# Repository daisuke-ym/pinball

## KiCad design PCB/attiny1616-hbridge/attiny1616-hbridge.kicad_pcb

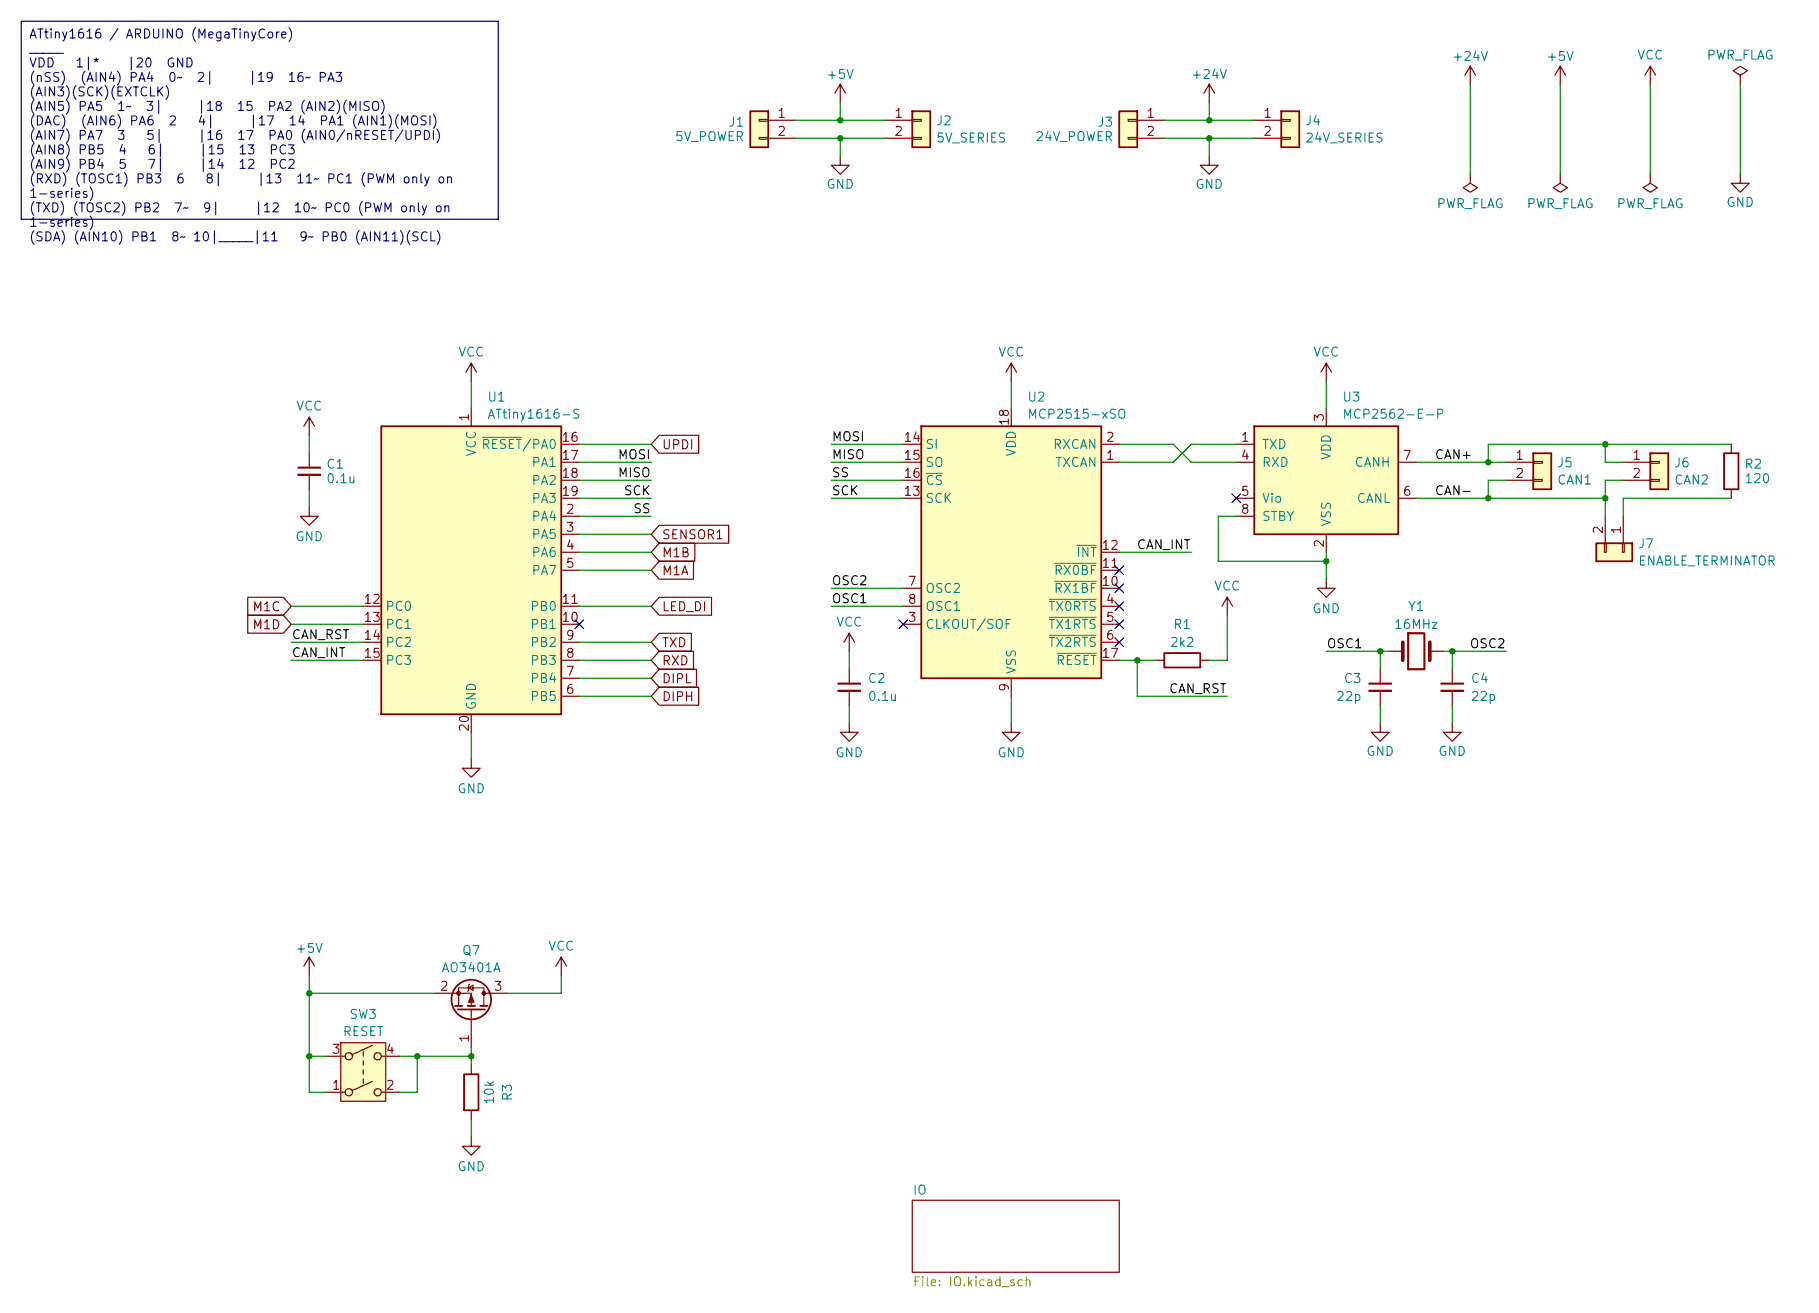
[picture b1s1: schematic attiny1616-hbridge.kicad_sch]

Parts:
C1, C2: 0.1u; C_0402_1005Metric; LCSC C307331
C3, C4: 22p; C_0402_1005Metric; LCSC C1555
J1: 5V_POWER; JST_XH_B2B-XH-A_1x02_P2.50mm_Vertical
J2: 5V_SERIES; JST_XH_B2B-XH-A_1x02_P2.50mm_Vertical
J3: 24V_POWER; JST_XH_B2B-XH-A_1x02_P2.50mm_Vertical
J4: 24V_SERIES; JST_XH_B2B-XH-A_1x02_P2.50mm_Vertical
J5: CAN1; JST_XH_B2B-XH-A_1x02_P2.50mm_Vertical
J6: CAN2; JST_XH_B2B-XH-A_1x02_P2.50mm_Vertical
J7: ENABLE_TERMINATOR; PinHeader_1x02_P2.54mm_Vertical
Q7: AO3401A; SOT-23; LCSC C15127
R1: 2k2; R_0402_1005Metric; LCSC C25879
R2: 120; R_0402_1005Metric; LCSC C25079
R3: 10k; R_0402_1005Metric; LCSC C25744
SW3: RESET; DTS-6-V-2
U1: ATtiny1616-S; SOIC-20W_7.5x12.8mm_P1.27mm
U2: MCP2515-xSO; DIP-18_W7.62mm_Socket
U3: MCP2562-E-P; DIP-8_W7.62mm
Y1: 16MHz; Crystal_SMD_3225-4Pin_3.2x2.5mm; LCSC C13738

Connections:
+5V: J1.1, J2.1, Q7.2 (S), SW3.1, SW3.3; also elsewhere on the board
+24V: J3.1, J4.1; also elsewhere on the board
/CAN+: J5.1, J6.1, R2.2, U3.7 (CANH)
/CAN-: J5.2, J6.2, J7.2, U3.6 (CANL)
/CAN_INT: U1.15 (PC3), U2.12 (~INT)
/CAN_RST: R1.1, U1.14 (PC2), U2.17 (~RESET)
/MISO: U1.18 (PA2), U2.15 (SO)
/MOSI: U1.17 (PA1), U2.14 (SI)
/OSC1: C3.1, U2.8 (OSC1), Y1.1
/OSC2: C4.1, U2.7 (OSC2), Y1.2
/SCK: U1.19 (PA3), U2.13 (SCK)
/SS: U1.2 (PA4), U2.16 (~CS)
DIPH: U1.6 (PB5); also elsewhere on the board
DIPL: U1.7 (PB4); also elsewhere on the board
GND: C1.2, C2.2, C3.2, C4.2, J1.2, J2.2, J3.2, J4.2, R3.2, U1.20 (GND), U2.9 (VSS), U3.2 (VSS), U3.8 (STBY); also elsewhere on the board
LED_DI: U1.11 (PB0); also elsewhere on the board
M1A: U1.5 (PA7); also elsewhere on the board
M1B: U1.4 (PA6); also elsewhere on the board
M1C: U1.12 (PC0); also elsewhere on the board
M1D: U1.13 (PC1); also elsewhere on the board
unnamed: J7.1, R2.1
unnamed: Q7.1 (G), R3.1, SW3.2, SW3.4
unnamed: U2.2 (RXCAN), U3.4 (RXD)
unnamed: U2.1 (TXCAN), U3.1 (TXD)
RXD: U1.8 (PB3); also elsewhere on the board
SENSOR1: U1.3 (PA5); also elsewhere on the board
TXD: U1.9 (PB2); also elsewhere on the board
UPDI: U1.16 (~RESET/PA0); also elsewhere on the board
VCC: C1.1, C2.1, Q7.3 (D), R1.2, U1.1 (VCC), U2.18 (VDD), U3.3 (VDD)

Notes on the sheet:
ATtiny1616 / ARDUINO (MegaTinyCore) _____ VDD 1|* |20 GND (nSS) (AIN4) PA4 0~ 2| |19 16~ PA3 (AIN3)(SCK)(EXTCLK) (AIN5) PA5 1~ 3| |18 15 PA2 (AIN2)(MISO) (DAC) (AIN6) PA6 2 4| |17 14 PA1 (AIN1)(MOSI) (AIN7) PA7 3 5| |16 17 PA0 (AIN0/nRESET/UPDI) (AIN8) PB5 4 6| |15 13 PC3 (AIN9) PB4 5 7| |14 12 PC2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

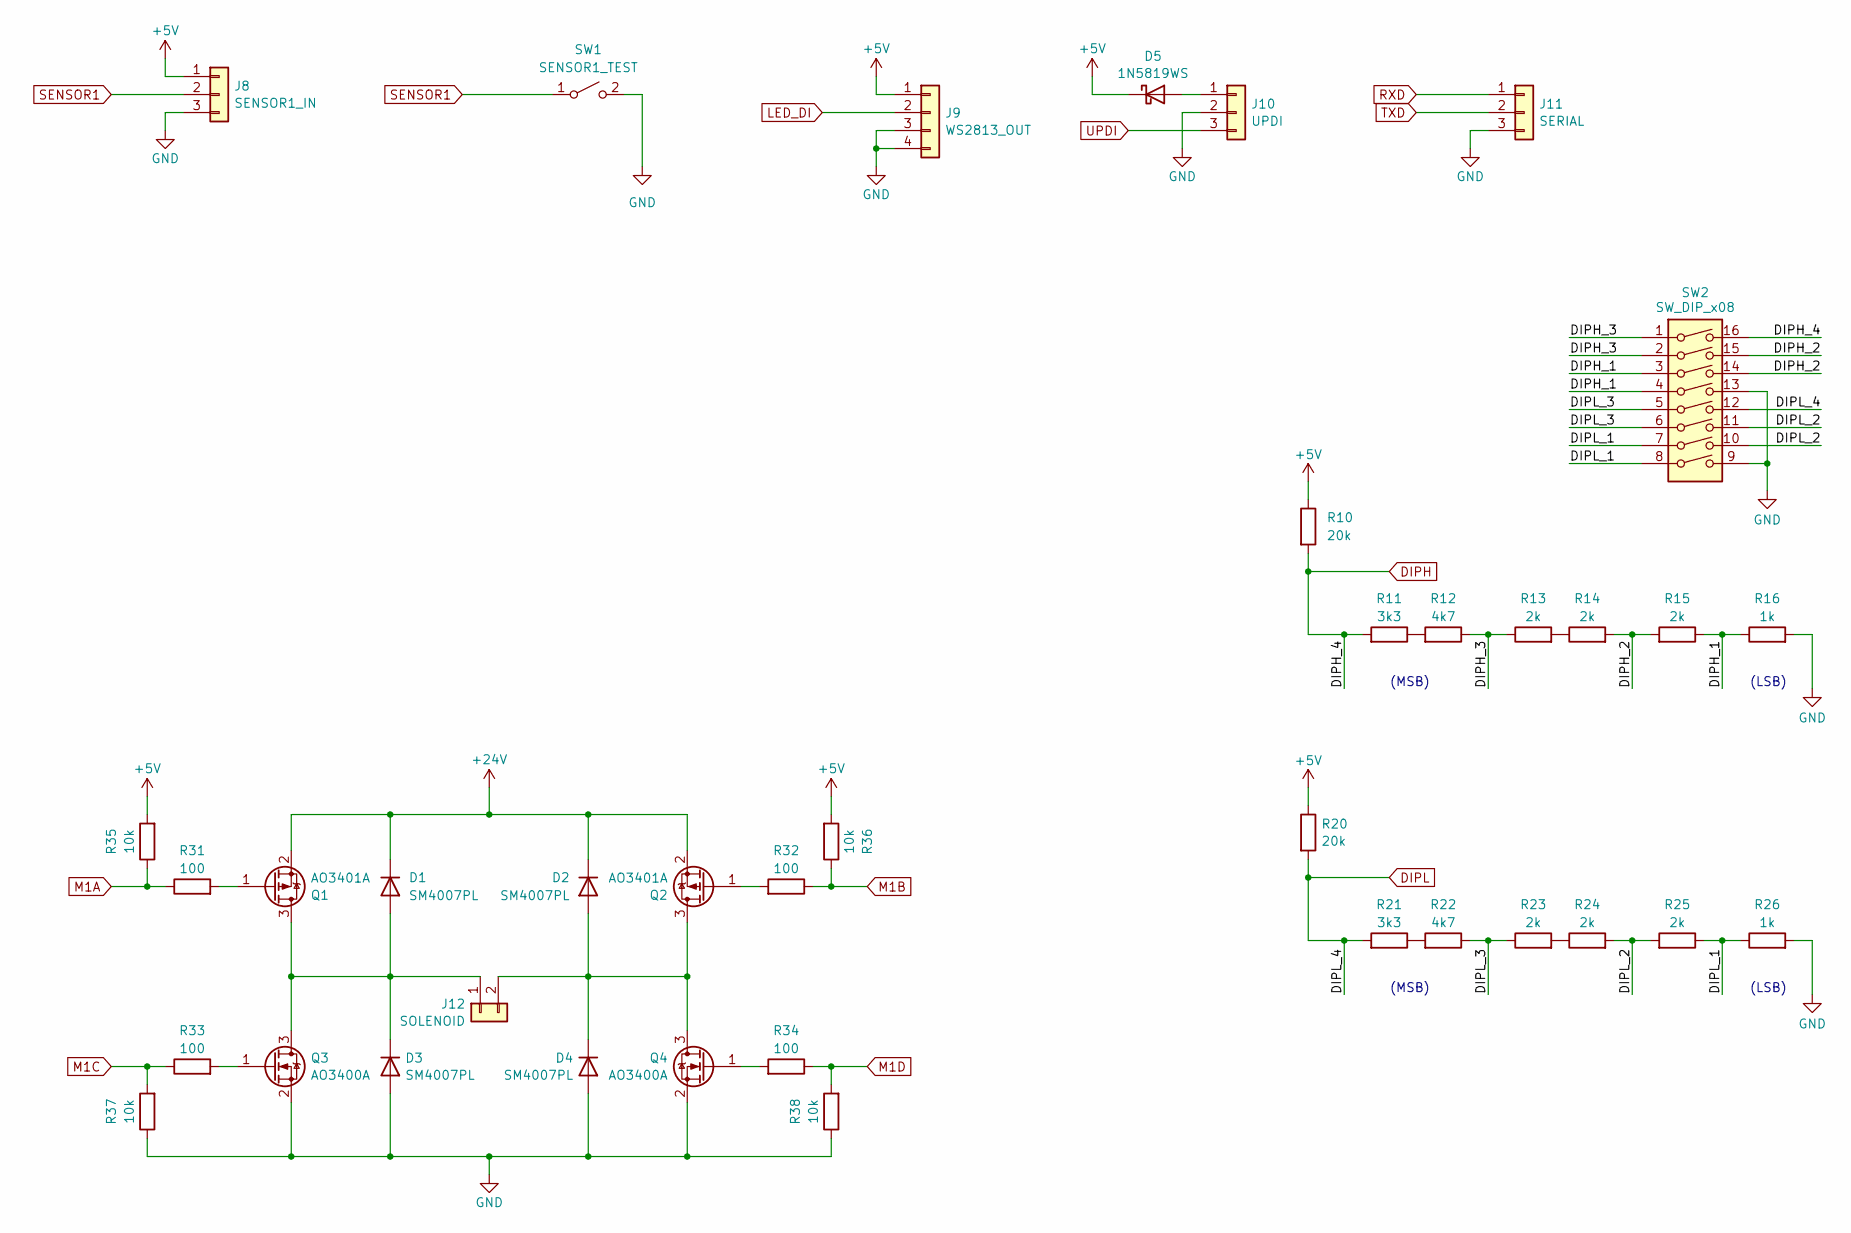
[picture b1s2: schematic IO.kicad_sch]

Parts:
D1, D2, D3, D4: SM4007PL; D_SOD-123F; LCSC C64898
D5: 1N5819WS; D_SOD-323; LCSC C191023
J8: SENSOR1_IN; JST_XH_B3B-XH-A_1x03_P2.50mm_Vertical
J9: WS2813_OUT; JST_XH_B4B-XH-A_1x04_P2.50mm_Vertical
J10: UPDI; PinHeader_1x03_P2.54mm_Vertical
J11: SERIAL; PinHeader_1x03_P2.54mm_Vertical
J12: SOLENOID; TB111-2-2
Q1, Q2: AO3401A; SOT-23; LCSC C15127
Q3, Q4: AO3400A; SOT-23; LCSC C20917
R10, R20: 20k; R_0402_1005Metric; LCSC C25765
R11, R21: 3k3; R_0402_1005Metric; LCSC C25890
R12, R22: 4k7; R_0402_1005Metric; LCSC C25900
R13, R14, R15, R23, R24, R25: 2k; R_0402_1005Metric; LCSC C4109
R16, R26: 1k; R_0402_1005Metric; LCSC C11702
R31, R32, R33, R34: 100; R_0402_1005Metric; LCSC C25077
R35, R36, R37, R38: 10k; R_0402_1005Metric; LCSC C25744
SW1: SENSOR1_TEST; TS-1088-AR02016; LCSC C720477
SW2: SW_DIP_x08; SW_DIP_SPSTx08_Slide_9.78x22.5mm_W7.62mm_P2.54mm

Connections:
+5V: D5.1 (K), J8.1, J9.1, R10.1, R20.1, R35.2, R36.2; also elsewhere on the board
+24V: D1.1 (K), D2.1 (K), Q1.2 (S), Q2.2 (S); also elsewhere on the board
/IO/DIPH_1: R15.1, R16.1, SW2.3, SW2.4
/IO/DIPH_2: R14.2, R15.2, SW2.14, SW2.15
/IO/DIPH_3: R12.1, R13.1, SW2.1, SW2.2
/IO/DIPL_1: R25.1, R26.1, SW2.7, SW2.8
/IO/DIPL_2: R24.2, R25.2, SW2.10, SW2.11
/IO/DIPL_3: R22.1, R23.1, SW2.5, SW2.6
DIPH: R10.2, R11.2, SW2.16; also elsewhere on the board
DIPL: R20.2, R21.2, SW2.12; also elsewhere on the board
GND: D3.2 (A), D4.2 (A), J8.3, J9.3, J9.4, J10.2, J11.3, Q3.2 (S), Q4.2 (S), R16.2, R26.2, R37.1, R38.1, SW1.2 (B), SW2.9, SW2.13; also elsewhere on the board
LED_DI: J9.2; also elsewhere on the board
M1A: R31.1, R35.1; also elsewhere on the board
M1B: R32.1, R36.1; also elsewhere on the board
M1C: R33.1, R37.2; also elsewhere on the board
M1D: R34.1, R38.2; also elsewhere on the board
unnamed: D1.2 (A), D3.1 (K), J12.1, Q1.3 (D), Q3.3 (D)
unnamed: D2.2 (A), D4.1 (K), J12.2, Q2.3 (D), Q4.3 (D)
unnamed: D5.2 (A), J10.1
unnamed: Q1.1 (G), R31.2
unnamed: Q2.1 (G), R32.2
unnamed: Q3.1 (G), R33.2
unnamed: Q4.1 (G), R34.2
unnamed: R11.1, R12.2
unnamed: R13.2, R14.1
unnamed: R21.1, R22.2
unnamed: R23.2, R24.1
RXD: J11.1; also elsewhere on the board
SENSOR1: J8.2, SW1.1 (A); also elsewhere on the board
TXD: J11.2; also elsewhere on the board
UPDI: J10.3; also elsewhere on the board

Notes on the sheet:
(LSB)
(MSB)

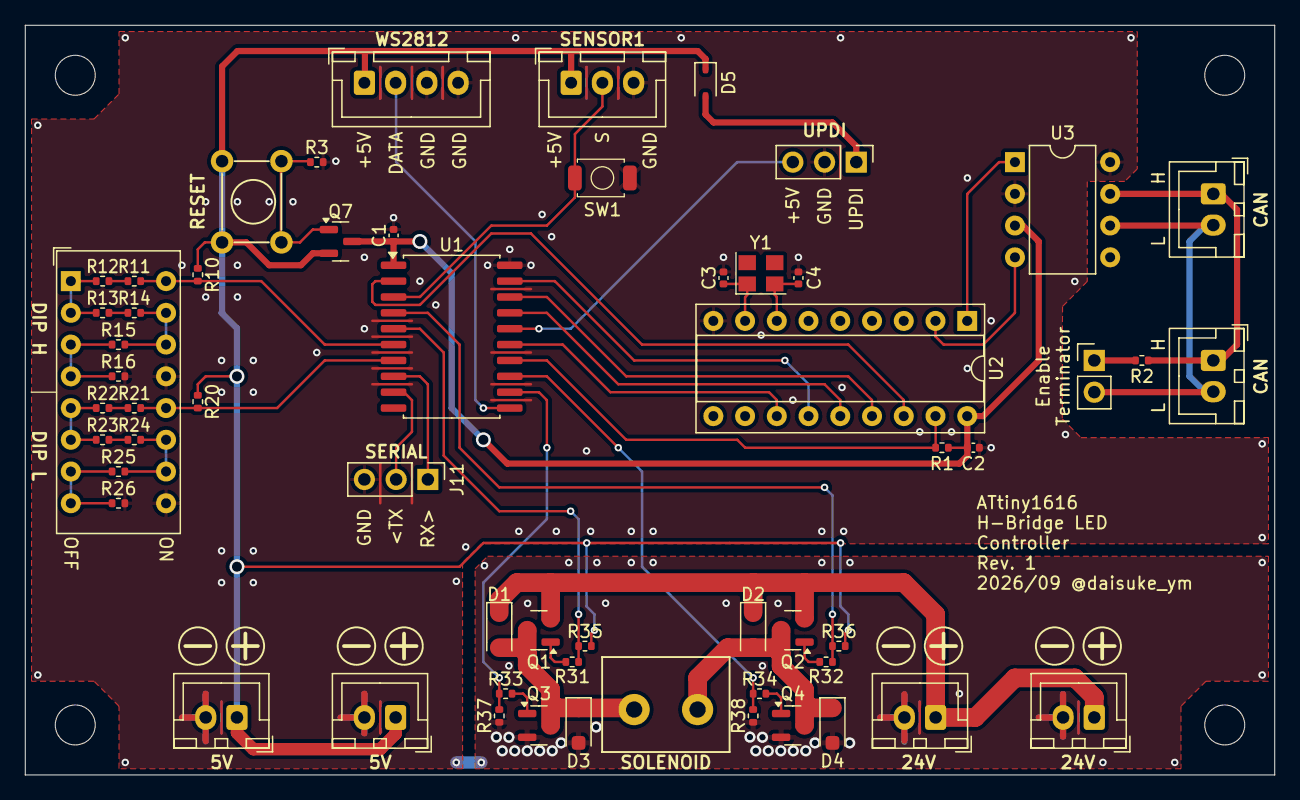
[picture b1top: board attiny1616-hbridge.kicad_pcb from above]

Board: 2 copper layers, 100.0 x 60.0 mm, 58 parts (0 on the bottom side), 46 nets.

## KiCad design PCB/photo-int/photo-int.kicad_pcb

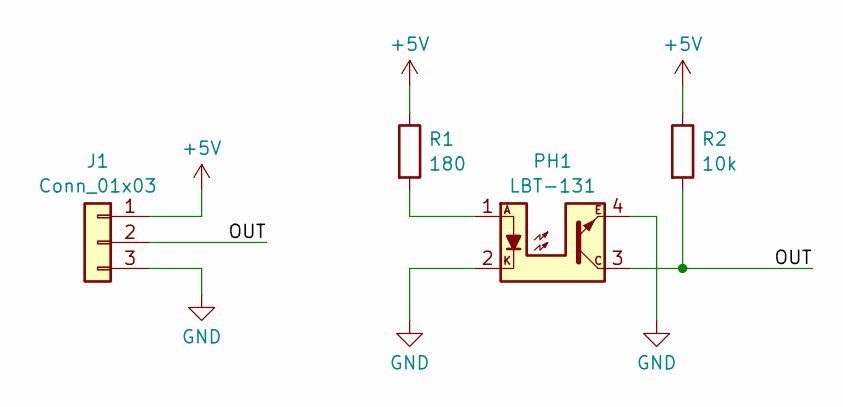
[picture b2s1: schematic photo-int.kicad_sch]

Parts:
J1: Conn_01x03; PinHeader_1x03_P2.54mm_Vertical
PH1: LBT-131
R1: 180; R_0603_1608Metric_Pad0.98x0.95mm_HandSolder
R2: 10k; R_0603_1608Metric_Pad0.98x0.95mm_HandSolder

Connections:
+5V: J1.1, R1.1, R2.1
/OUT: J1.2, PH1.3, R2.2
GND: J1.3, PH1.2, PH1.4
unnamed: PH1.1, R1.2

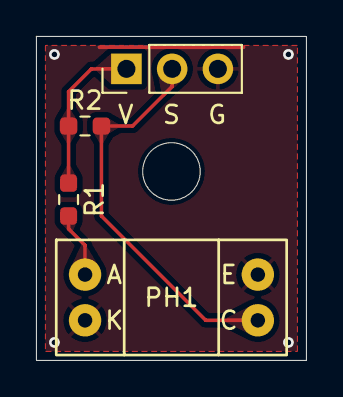
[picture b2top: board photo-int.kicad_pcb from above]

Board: 2 copper layers, 15.0 x 18.0 mm, 4 parts (0 on the bottom side), 4 nets.

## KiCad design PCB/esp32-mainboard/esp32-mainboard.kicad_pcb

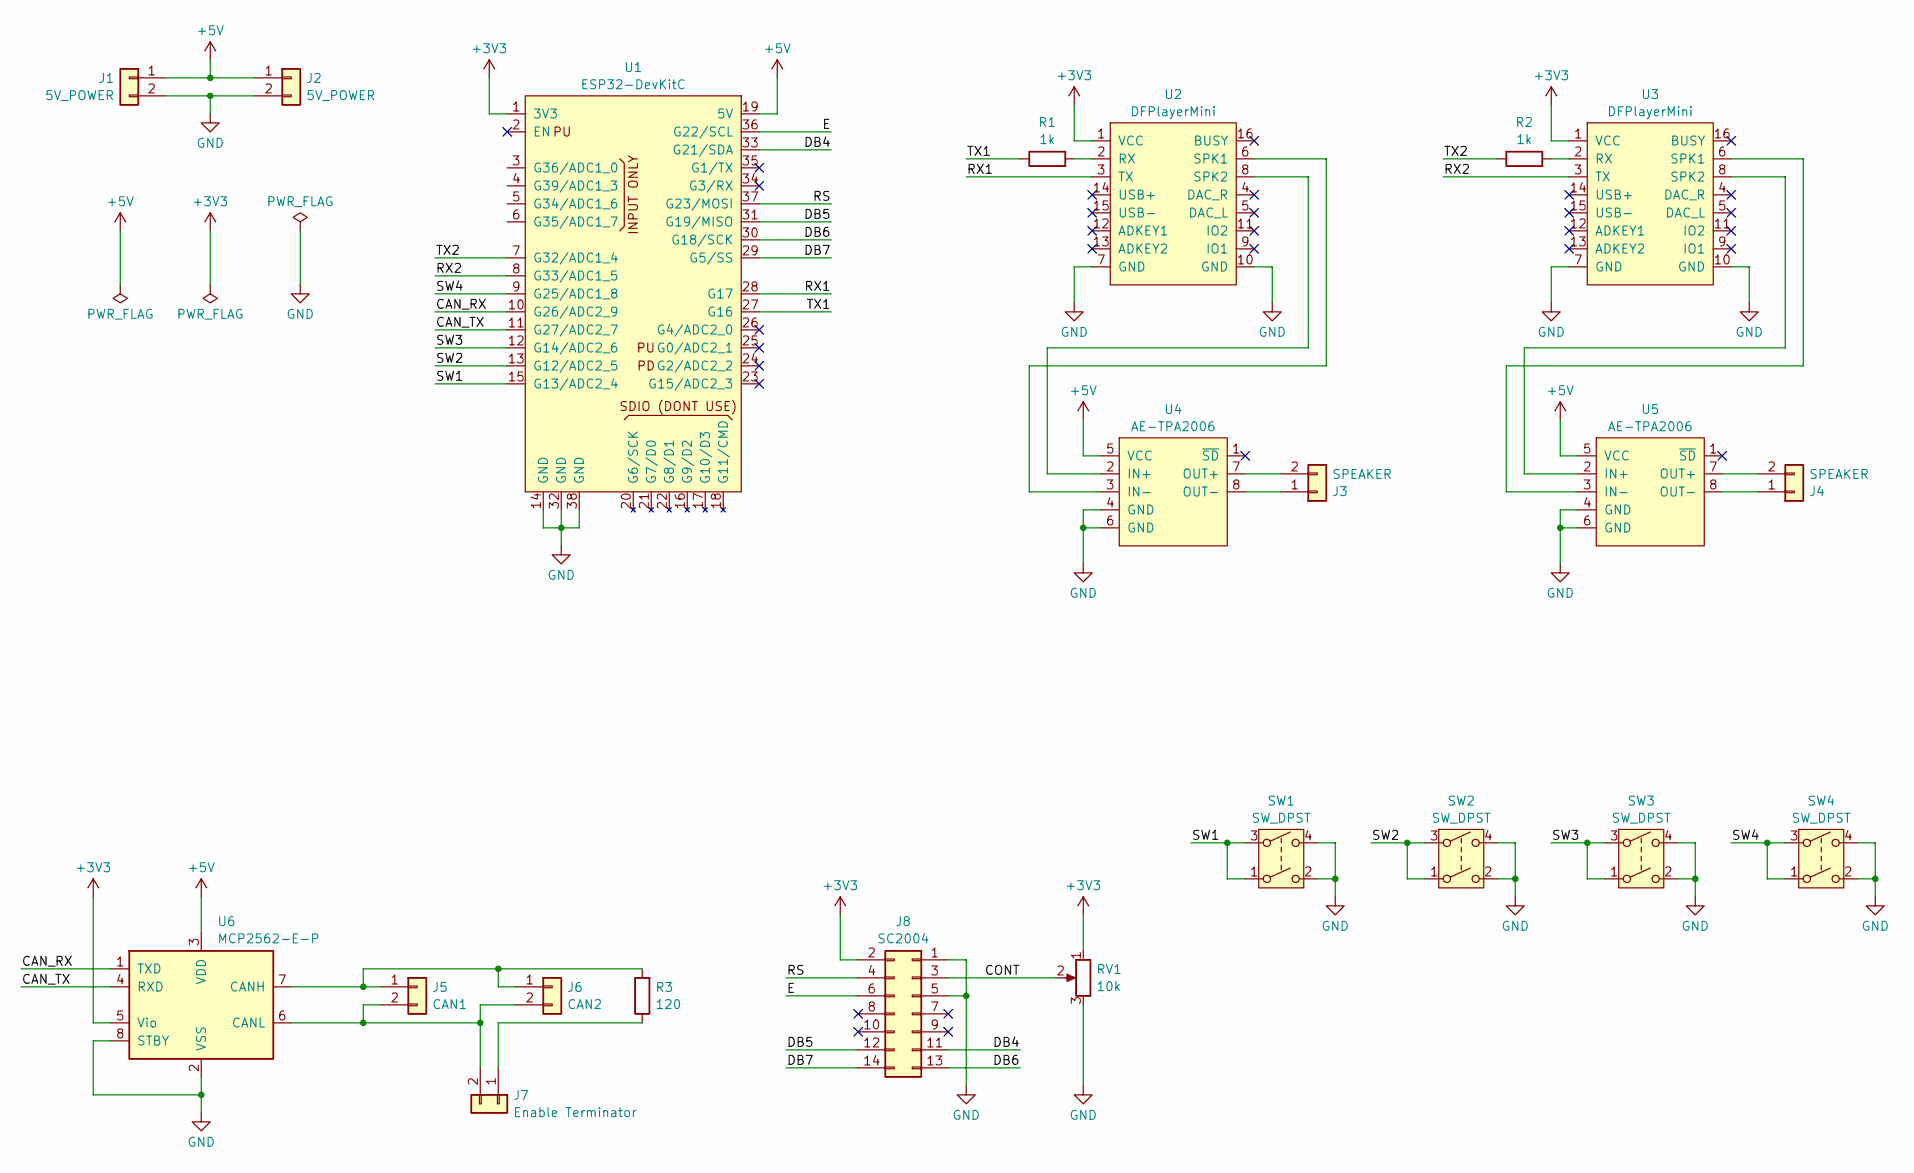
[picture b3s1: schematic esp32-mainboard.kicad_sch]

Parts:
J1, J2: 5V_POWER; JST_XH_B2B-XH-A_1x02_P2.50mm_Vertical
J3, J4: SPEAKER; JST_XH_B2B-XH-A_1x02_P2.50mm_Vertical
J5: CAN1; JST_XH_B2B-XH-A_1x02_P2.50mm_Vertical
J6: CAN2; JST_XH_B2B-XH-A_1x02_P2.50mm_Vertical
J7: Enable Terminator; PinHeader_1x02_P2.54mm_Vertical
J8: SC2004; PinHeader_2x07_P2.54mm_Vertical
R1, R2: 1k; R_Axial_DIN0207_L6.3mm_D2.5mm_P10.16mm_Horizontal
R3: 120; R_Axial_DIN0207_L6.3mm_D2.5mm_P10.16mm_Horizontal
RV1: 10k; Potentiometer_Bourns_3339P_Vertical
SW1, SW2, SW3, SW4: SW_DPST; DTS-6-V-2
U1: ESP32-DevKitC
U2, U3: DFPlayerMini
U4, U5: AE-TPA2006; PinSocket_1x08_P2.54mm_Vertical
U6: MCP2562-E-P; DIP-8_W7.62mm

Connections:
+3V3: J8.2, RV1.1, U1.1 (3V3), U2.1 (VCC), U3.1 (VCC), U6.5 (Vio)
+5V: J1.1, J2.1, U1.19 (5V), U4.5 (VCC), U5.5 (VCC), U6.3 (VDD)
/CAN_RX: U1.10 (G26/ADC2_9), U6.1 (TXD)
/CAN_TX: U1.11 (G27/ADC2_7), U6.4 (RXD)
/CONT: J8.3, RV1.2
/DB4: J8.11, U1.33 (G21/SDA)
/DB5: J8.12, U1.31 (G19/MISO)
/DB6: J8.13, U1.30 (G18/SCK)
/DB7: J8.14, U1.29 (G5/SS)
/E: J8.6, U1.36 (G22/SCL)
/RS: J8.4, U1.37 (G23/MOSI)
/RX1: U1.28 (G17), U2.3 (TX)
/RX2: U1.8 (G33/ADC1_5), U3.3 (TX)
/SW1: SW1.1, SW1.3, U1.15 (G13/ADC2_4)
/SW2: SW2.1, SW2.3, U1.13 (G12/ADC2_5)
/SW3: SW3.1, SW3.3, U1.12 (G14/ADC2_6)
/SW4: SW4.1, SW4.3, U1.9 (G25/ADC1_8)
/TX1: R1.1, U1.27 (G16)
/TX2: R2.1, U1.7 (G32/ADC1_4)
GND: J1.2, J2.2, J8.1, J8.5, RV1.3, SW1.2, SW1.4, SW2.2, SW2.4, SW3.2, SW3.4, SW4.2, SW4.4, U1.14 (GND), U1.32 (GND), U1.38 (GND), U2.7 (GND), U2.10 (GND), U3.7 (GND), U3.10 (GND), U4.4 (GND), U4.6 (GND), U5.4 (GND), U5.6 (GND), U6.2 (VSS), U6.8 (STBY)
unnamed: J3.1, U4.8 (OUT-)
unnamed: J3.2, U4.7 (OUT+)
unnamed: J4.1, U5.8 (OUT-)
unnamed: J4.2, U5.7 (OUT+)
unnamed: J5.1, J6.1, R3.2, U6.7 (CANH)
unnamed: J5.2, J6.2, J7.2, U6.6 (CANL)
unnamed: J7.1, R3.1
unnamed: R1.2, U2.2 (RX)
unnamed: U2.6 (SPK1), U4.3 (IN-)
unnamed: U2.8 (SPK2), U4.2 (IN+)
unnamed: R2.2, U3.2 (RX)
unnamed: U3.6 (SPK1), U5.3 (IN-)
unnamed: U3.8 (SPK2), U5.2 (IN+)

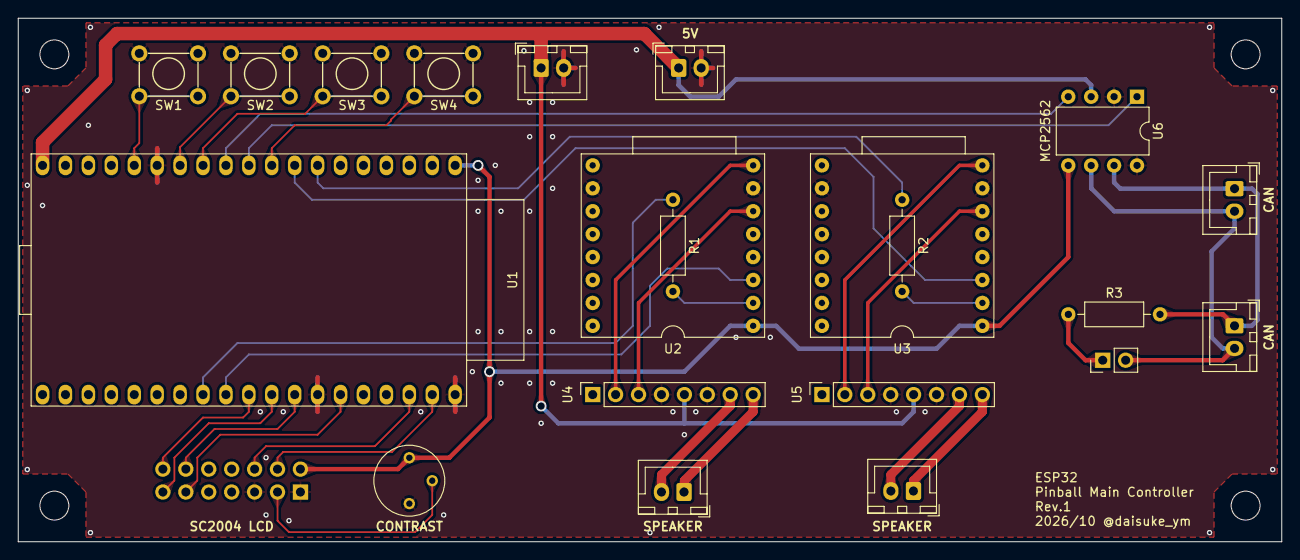
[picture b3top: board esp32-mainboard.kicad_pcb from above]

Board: 2 copper layers, 140.0 x 58.0 mm, 26 parts (1 on the bottom side), 33 nets.

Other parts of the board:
MH1, MH2, MH3, MH4: MountingHole_3.2mm_M3

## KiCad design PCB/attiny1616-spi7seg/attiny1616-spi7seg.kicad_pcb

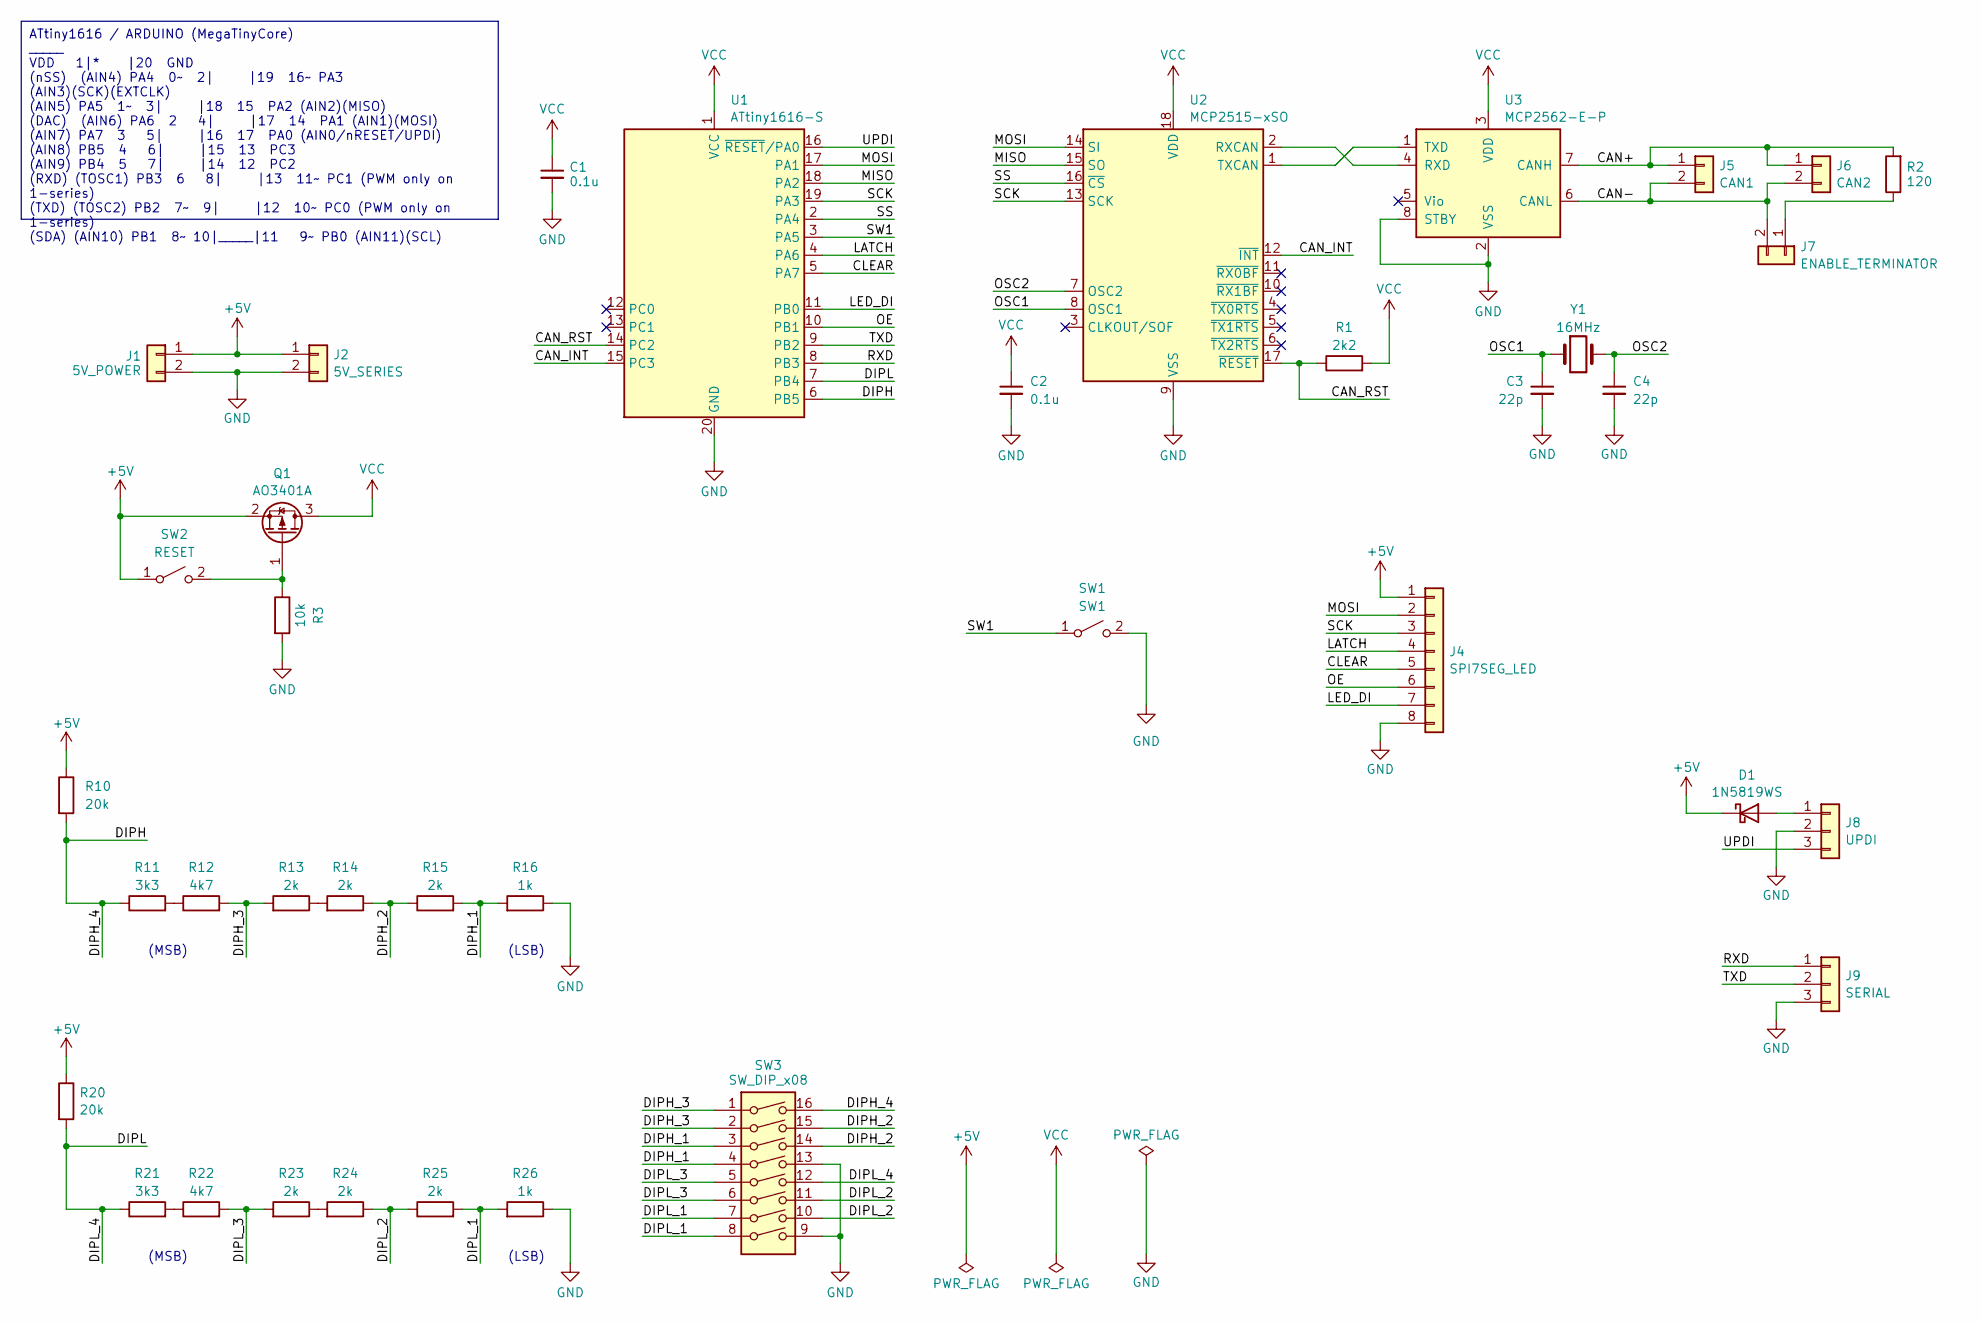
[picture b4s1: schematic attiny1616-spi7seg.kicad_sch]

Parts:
C1, C2: 0.1u; C_0402_1005Metric; LCSC C307331
C3, C4: 22p; C_0402_1005Metric; LCSC C1555
D1: 1N5819WS; D_SOD-323; LCSC C191023
J1: 5V_POWER; JST_XH_B2B-XH-A_1x02_P2.50mm_Vertical
J2: 5V_SERIES; JST_XH_B2B-XH-A_1x02_P2.50mm_Vertical
J4: SPI7SEG_LED; PinHeader_1x08_P2.54mm_Vertical
J5: CAN1; JST_XH_B2B-XH-A_1x02_P2.50mm_Vertical
J6: CAN2; JST_XH_B2B-XH-A_1x02_P2.50mm_Vertical
J7: ENABLE_TERMINATOR; PinHeader_1x02_P2.54mm_Vertical
J8: UPDI; PinHeader_1x03_P2.54mm_Vertical
J9: SERIAL; PinHeader_1x03_P2.54mm_Vertical
Q1: AO3401A; SOT-23; LCSC C15127
R1: 2k2; R_0402_1005Metric; LCSC C25879
R2: 120; R_0402_1005Metric; LCSC C25079
R3: 10k; R_0402_1005Metric; LCSC C25744
R10, R20: 20k; R_0402_1005Metric; LCSC C25765
R11, R21: 3k3; R_0402_1005Metric; LCSC C25890
R12, R22: 4k7; R_0402_1005Metric; LCSC C25900
R13, R14, R15, R23, R24, R25: 2k; R_0402_1005Metric; LCSC C4109
R16, R26: 1k; R_0402_1005Metric; LCSC C11702
SW1: SW1; TS-1088-AR02016; LCSC C720477
SW2: RESET; TS-1088-AR02016; LCSC C720477
SW3: SW_DIP_x08; SW_DIP_SPSTx08_Slide_9.78x22.5mm_W7.62mm_P2.54mm
U1: ATtiny1616-S; SOIC-20W_7.5x12.8mm_P1.27mm
U2: MCP2515-xSO; DIP-18_W7.62mm_Socket
U3: MCP2562-E-P; DIP-8_W7.62mm
Y1: 16MHz; Crystal_SMD_3225-4Pin_3.2x2.5mm; LCSC C13738

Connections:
+5V: D1.1 (K), J1.1, J2.1, J4.1, Q1.2 (S), R10.1, R20.1, SW2.1 (A)
/CAN+: J5.1, J6.1, R2.2, U3.7 (CANH)
/CAN-: J5.2, J6.2, J7.2, U3.6 (CANL)
/CAN_INT: U1.15 (PC3), U2.12 (~INT)
/CAN_RST: R1.1, U1.14 (PC2), U2.17 (~RESET)
/CLEAR: J4.5, U1.5 (PA7)
/DIPH: R10.2, R11.1, SW3.16, U1.6 (PB5)
/DIPH_1: R15.2, R16.2, SW3.3, SW3.4
/DIPH_2: R14.1, R15.1, SW3.14, SW3.15
/DIPH_3: R12.2, R13.2, SW3.1, SW3.2
/DIPL: R20.2, R21.1, SW3.12, U1.7 (PB4)
/DIPL_1: R25.2, R26.2, SW3.7, SW3.8
/DIPL_2: R24.1, R25.1, SW3.10, SW3.11
/DIPL_3: R22.2, R23.2, SW3.5, SW3.6
/LATCH: J4.4, U1.4 (PA6)
/LED_DI: J4.7, U1.11 (PB0)
/MISO: U1.18 (PA2), U2.15 (SO)
/MOSI: J4.2, U1.17 (PA1), U2.14 (SI)
/OE: J4.6, U1.10 (PB1)
/OSC1: C3.1, U2.8 (OSC1), Y1.1
/OSC2: C4.1, U2.7 (OSC2), Y1.2
/RXD: J9.1, U1.8 (PB3)
/SCK: J4.3, U1.19 (PA3), U2.13 (SCK)
/SS: U1.2 (PA4), U2.16 (~CS)
/SW1: SW1.1 (A), U1.3 (PA5)
/TXD: J9.2, U1.9 (PB2)
/UPDI: J8.3, U1.16 (~RESET/PA0)
GND: C1.2, C2.2, C3.2, C4.2, J1.2, J2.2, J4.8, J8.2, J9.3, R3.2, R16.1, R26.1, SW1.2 (B), SW3.9, SW3.13, U1.20 (GND), U2.9 (VSS), U3.2 (VSS), U3.8 (STBY)
unnamed: D1.2 (A), J8.1
unnamed: J7.1, R2.1
unnamed: Q1.1 (G), R3.1, SW2.2 (B)
unnamed: R11.2, R12.1
unnamed: R13.1, R14.2
unnamed: R21.2, R22.1
unnamed: R23.1, R24.2
unnamed: U2.2 (RXCAN), U3.4 (RXD)
unnamed: U2.1 (TXCAN), U3.1 (TXD)
VCC: C1.1, C2.1, Q1.3 (D), R1.2, U1.1 (VCC), U2.18 (VDD), U3.3 (VDD)

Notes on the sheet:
ATtiny1616 / ARDUINO (MegaTinyCore) _____ VDD 1|* |20 GND (nSS) (AIN4) PA4 0~ 2| |19 16~ PA3 (AIN3)(SCK)(EXTCLK) (AIN5) PA5 1~ 3| |18 15 PA2 (AIN2)(MISO) (DAC) (AIN6) PA6 2 4| |17 14 PA1 (AIN1)(MOSI) (AIN7) PA7 3 5| |16 17 PA0 (AIN0/nRESET/UPDI) (AIN8) PB5 4 6| |15 13 PC3 (AIN9) PB4 5 7| |14 12 PC2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
(LSB)
(MSB)

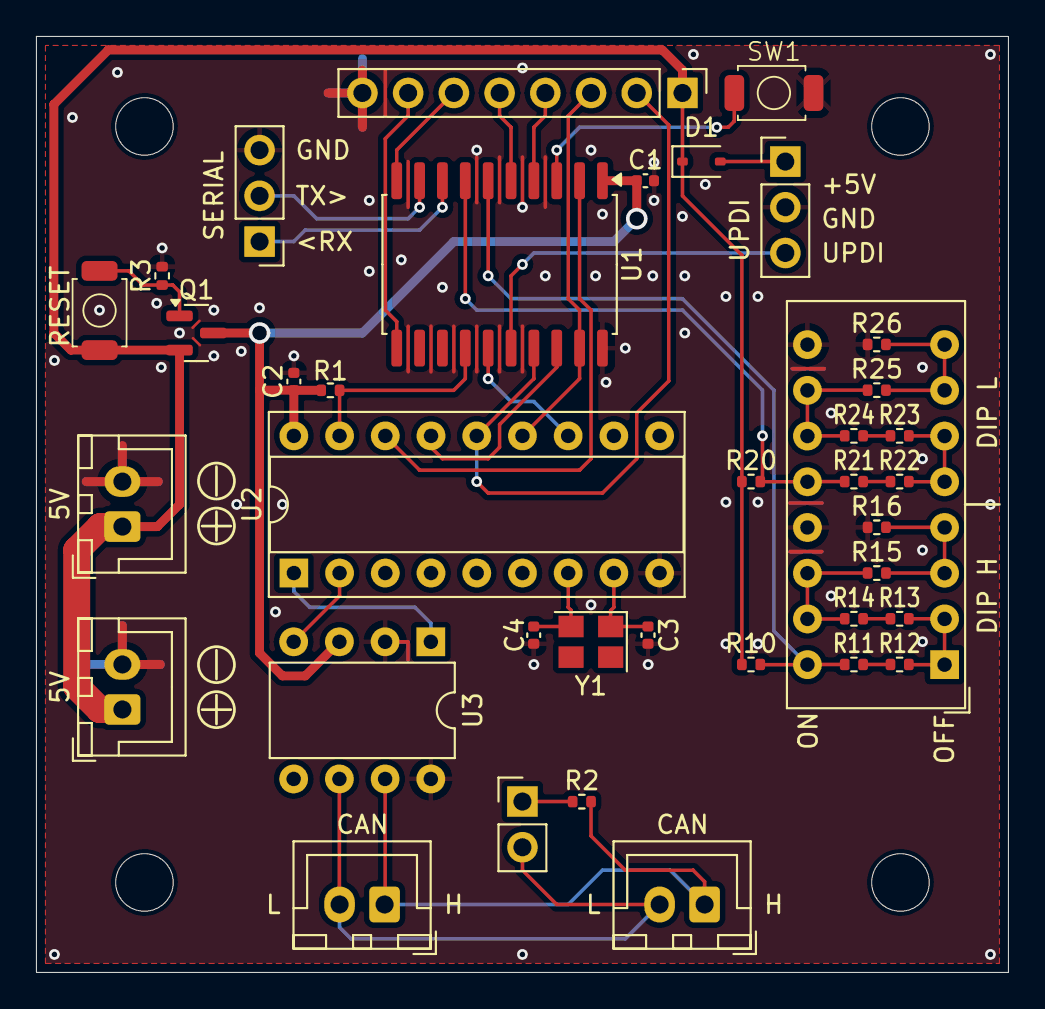
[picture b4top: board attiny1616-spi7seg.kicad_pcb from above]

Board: 2 copper layers, 54.0 x 52.0 mm, 38 parts (0 on the bottom side), 38 nets.

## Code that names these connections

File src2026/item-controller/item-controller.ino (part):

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
// ----------------------------------------------------------------------
// ピン割り当て
const byte SENSOR1 = 1;
const byte SENSOR2 = 2;
const byte SENSOR3 = 3;

const byte DIPH = 4;
const byte DIPL = 5;

const byte SOL1 = 10;
const byte SOL2 = 11;

// 7セグあり基板用。SENSORxと被っているがプリプロセッサで振り分けしているので問題なし
const byte LATCH = 2; 
const byte CLR = 3;
const byte OE = 8;

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  pinMode(LEDPIN, OUTPUT);
  #if defined(DTARGET) || defined(STARGET)
    // DTARGET、STARGETセンサーは検知でHIGHなのでプルアップしない
    pinMode(SENSOR1, INPUT);
  #else
    pinMode(SENSOR1, INPUT_PULLUP);
  #endif
  #if defined(TIMER7SEG) || defined(SCOREBOARD)
    pinMode(LATCH, OUTPUT);
    pinMode(OE, OUTPUT);
    pinMode(CLR, OUTPUT);
    digitalWrite(CLR, LOW);
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
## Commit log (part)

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2025-10-21 CAN通信の内容をLCDとシリアルモニタに表示するためのコードを追加しました。
2025-10-21 シリアル通信で受信したCANデータを処理し、CANバスに送信する機能を追加しました。
2025-10-21 待機時はLEDが七色に変化、 コマンドを受け取ると、カウントダウン、停止を行う。
2025-10-22 タイマーのコマンド定義を修正した。
2025-10-22 Revert "タイマーのコマンド定義を修正した。"
    This reverts commit 36e2042de882faaccff6d24737135bc5fc7ae6d7.
2025-10-22 得点表示板コントローラの初回コミット
2025-10-22 得点表示板のコマンド定義を修正しました。
2025-10-22 テレメトリー送信間隔を5秒に変更した。
2025-10-22 タイマーからのテレメトリ情報をLCDに表示する機能を追加した。
2025-10-22 ドロップターゲットコントローラの初回コミット
2025-10-22 ドロップターゲットからのテレメトリ情報をLCDに表示する機能を追加した。
2025-10-23 ジャンパーコントローラの初回コミット
2025-10-23 ジャンパーからのテレメトリ情報をLCDに表示する機能を追加した。
2025-10-23 受信フィルターをCANIDに合わせて設定するように修正した。
2025-10-23 定期的にテレメトリ情報を送信するコードを追加した。
2025-10-24 ハイスコアをEEPROMに保存・読み込みする機能を追加した。
2025-10-24 得点板制御コマンドを追加した。
2025-10-24 スタンダップターゲットの初回コミット
2025-10-24 スタンダップターゲットのテレメトリ情報をLCDに表示する機能を追加した。
2025-10-24 スリングショットからのテレメトリ情報をLCDに表示する機能を追加した。
2025-10-24 ドロップターゲット、スリングショットの表示位置を修正した。
2025-10-24 スリングショットコントローラの初回コミット
2025-10-28 バンパーコントローラの初回コミット
2025-10-28 コマンドの定義を修正した。
2025-10-28 バンパーのテレメトリ情報をLCDに表示する機能を追加した。
2025-10-28 アクションがあったときに、その状態をCANで送信するように変更した。
2025-10-28 ドロップターゲットのテレメトリ情報の表示方法を変更した。
2025-10-28 ボールセパレータ・コントローラの初回コミット
2025-10-28 ボールスルー、ボールセパレーターのテレメトリ情報をLCDに表示する機能を追加した。
2025-10-28 テレメトリ情報を変更した。
2025-10-28 ジャンパーのテレメトリ情報の表示方法を変更した。
2025-10-29 タイマーだけを動かすブランチ。 タイマーと同時にLEDを制御しようとすると、CAN通信が不安定になるため、 一旦LED制御を外す。
2025-10-29 アウトホールのテレメトリ情報をLCDに表示するようにした。
2025-10-29 LCDの表示方法を修正して、各種情報が見やすくなるようにしました。
2025-10-29 アウトホールコントローラの初回コミット
2025-10-29 エクストラボールコントローラの初回コミット
2025-10-29 制御の方法を変更した。
2025-10-29 エクストラボールのテレメトリ情報をLCDに表示するようにしました。
2025-10-30 ゲーム中かどうかを送信するように修正した。
2025-10-30 LibreOfficeのロックファイルを無視するようにした。
2025-10-30 defines.h を def-can.h と def-vars.h に分割しました。
2025-10-30 ゲーム開始前に盤面の初期化をする関数を追加した。
2025-10-30 次のアイテムのHITで得点を加算する機能を実装しました： - ボールセパレータ - ボールスルー - バンパー
2025-10-30 次のアイテムのHITで得点を加算する機能を実装しました： - スタンダップターゲット - スリングショット
2025-10-30 次のアイテムのHITで得点を加算する機能を実装しました： - ジャンパー - エクストラボール
2025-10-30 次のアイテムのHITで得点を加算する機能を実装しました： - ドロップターゲット - タイマー
    ドロップターゲットのどれかに当てることでタイマー開始
    時間内に全てのドロップターゲットを上げると次のステージへ
    ステージが上がると得点の倍率が上がるようにしました。
2025-10-30 スコア送信時のデバッグメッセージを表示しないように修正
2025-10-30 受信したCANメッセージをシリアルに表示しないようにした
2025-10-30 IDEの設定ファイルを修正
2025-10-30 スタートボタンでBGM再生、ゲームオーバーで停止する機能を実装 ステージ遷移でBGMを切り替える機能を実装
2025-10-31 シリアル通信で受信したコマンドに基づき、DFPlayerMiniを操作する機能を追加しました。
2025-10-31 コマンド受信時のアンサーバックを追加して、通信の信頼性を向上させる。
2025-10-31 ステージ番号表示機能を追加した。 NeoPixel LEDの制御コードを削除した。
2025-10-31 ステージ番号をタイマーに表示するようにした。
2025-10-31 ボールが落ちた時、盤面を初期化するよう修正
2025-10-31 ヘッダファイルのコメントが不適切だったのを修正
2025-10-31 効果音用の定義を追加
2025-10-31 ボールが落ちたとき、得点までクリアされてしまっていた問題を修正
2025-10-31 ステージ番号送信処理をgame_logic()の中からinit_board()の中に移動しました。
